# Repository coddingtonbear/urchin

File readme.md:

# Urchin: Atmel Programmer with onboard 8-pin ATTiny pad

Everybody makes their own programmer someday.  What this does in addition
to all of the normal things you'd expect a programmer to do is include
an 8-pin ATTiny pad allowing you to program an ATTiny on-the-fly by
pressing it onto the unpopulated pad during programming.

## Schematic

## Fuse Settings

We need slightly-nonstandard fuse settings so we can run both the microcontroller
and the CH340 UART to USB adapter using the same 12MHz clock; these will differ
from the default 12MHz settings in only the Low bit having CKOUT enabled.

* Low: 0xbf
* High: 0xde
* Extended: 0xfd

## Enclosure

You can also find a 3d-printable enclosure in the 'enclosure' folder.

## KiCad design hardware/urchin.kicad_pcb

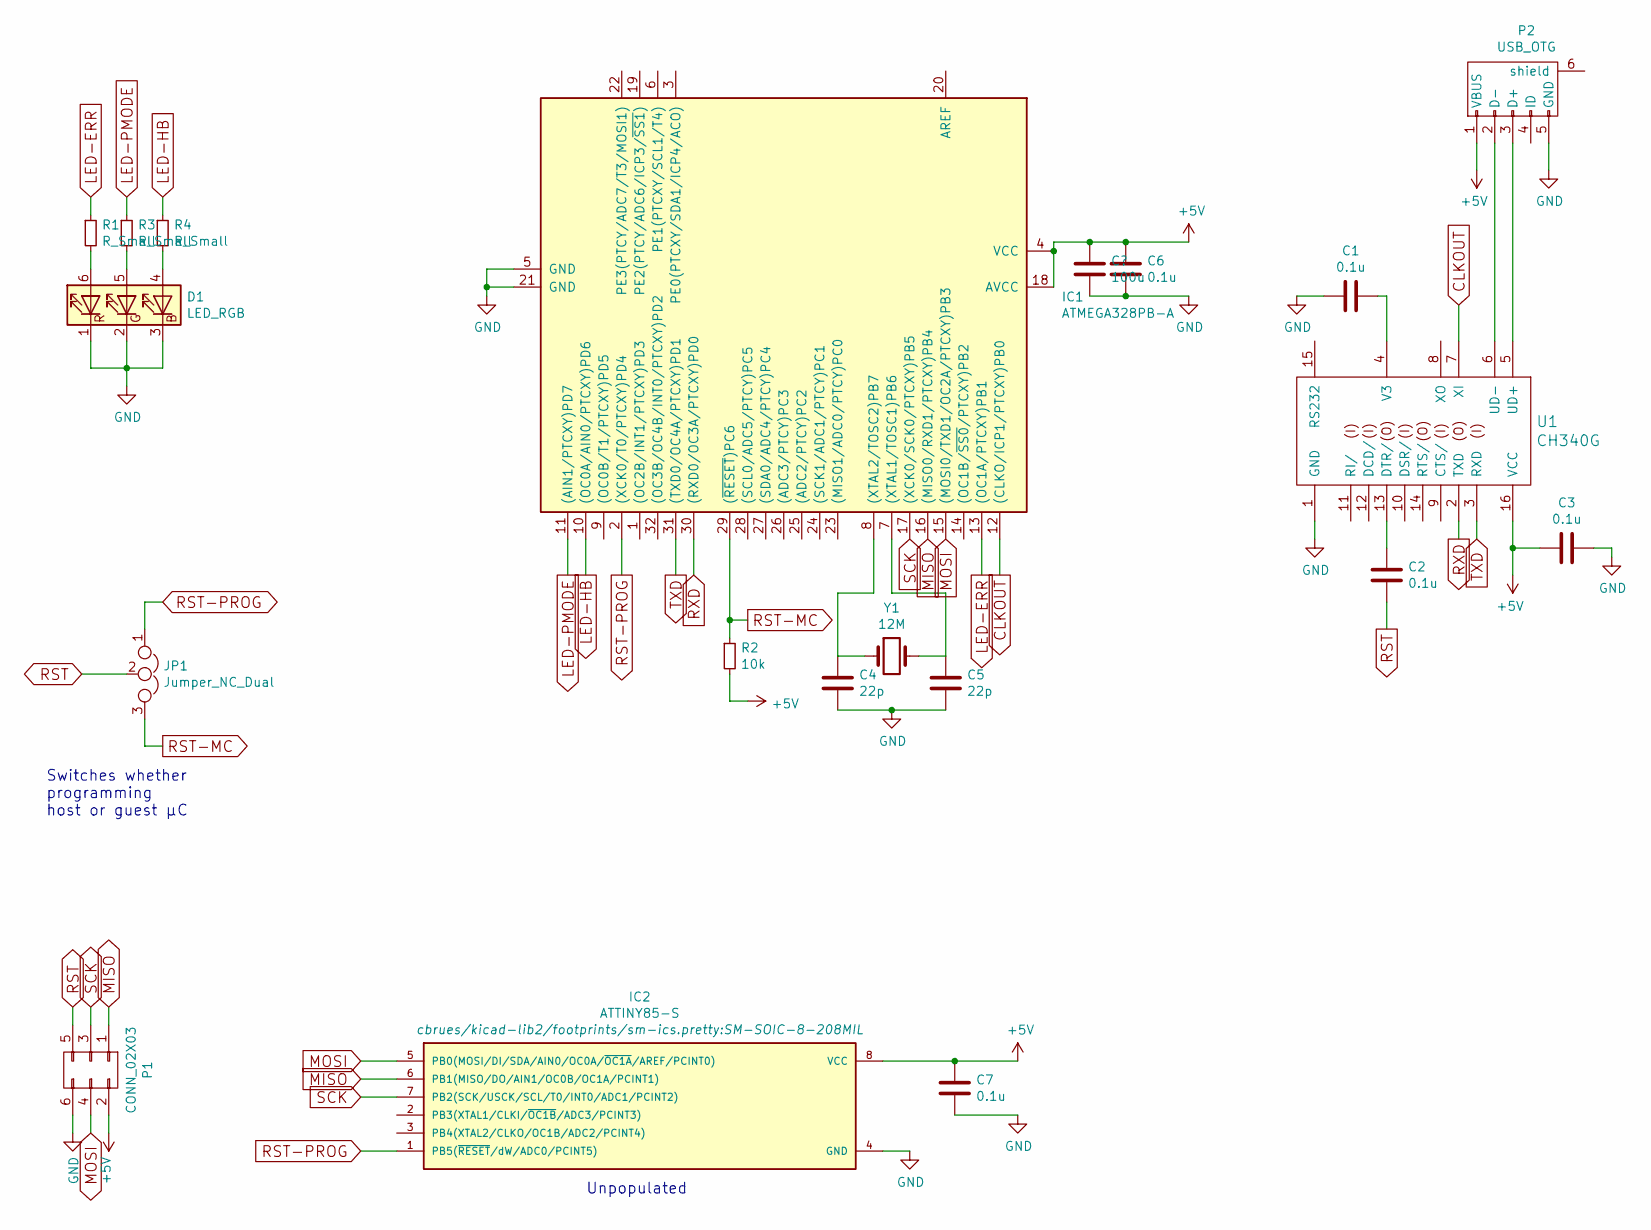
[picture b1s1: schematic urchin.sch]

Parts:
C1, C2, C3, C6, C7: 0.1u; C_0805_HandSoldering
C4, C5: 22p; C_0805_HandSoldering
D1: LED_RGB; SLV6A-FKB
IC1: ATMEGA328PB-A; TQFP32_ATMEGA328P
IC2: ATTINY85-S; SM-SOIC-8-208MIL
JP1: Jumper_NC_Dual; Pin_Header_Straight_1x03_Pitch2.54mm_SMD_Pin1Left
P1: CONN_02X03; SMD_PIN_HEADER_02x03
P2: USB_OTG; MICRO-B_USB-INVERTED
R1, R3, R4: R_Small; R_0805_HandSoldering
R2: 10k; R_0805_HandSoldering
U1: CH340G; SOIC-16_3.9x9.9mm_Pitch1.27mm
Y1: 12M; Crystal_SMD_HC49-SD

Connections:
+5V: C3.1, C6.1, C7.1, IC1.4 (VCC), IC1.18 (AVCC), IC2.8 (VCC), P1.2, P2.1 (VBUS), R2.2, U1.16 (VCC); also elsewhere on the board
CLKOUT: IC1.12 ((CLKO/ICP1/PTCXY)PB0), U1.7 (XI)
GND: C1.1, C3.2, C4.2, C5.2, C6.2, C7.2, D1.1 (RK), D1.2 (GK), D1.3 (BK), IC1.5 (GND), IC1.21 (GND), IC2.4 (GND), P1.6, P2.5 (GND), U1.1 (GND); also elsewhere on the board
LED-ERR: IC1.13 ((OC1A/PTCXY)PB1), R1.1
LED-HB: IC1.10 ((OC0A/AIN0/PTCXY)PD6), R4.1
LED-PMODE: IC1.11 ((AIN1/PTCXY)PD7), R3.1
MISO: IC1.16 ((MISO0/RXD1/PTCXY)PB4), IC2.6 (PB1(MISO/DO/AIN1/OC0B/OC1A/PCINT1)), P1.1
MOSI: IC1.15 ((MOSI0/TXD1/OC2A/PTCXY)PB3), IC2.5 (PB0(MOSI/DI/SDA/AIN0/OC0A/~OC1A~/AREF/P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), P1.4
unnamed: C1.2, U1.4 (V3)
unnamed: C2.1, U1.13 (DTR/)
unnamed: C4.1, IC1.8 ((XTAL2/TOSC2)PB7), Y1.1
unnamed: C5.1, IC1.7 ((XTAL1/TOSC1)PB6), Y1.2
unnamed: D1.4 (BA), R4.2
unnamed: D1.5 (GA), R3.2
unnamed: D1.6 (RA), R1.2
unnamed: P2.2 (D-), U1.6 (UD-)
unnamed: P2.3 (D+), U1.5 (UD+)
RST: C2.2, JP1.2, P1.5
RST-MC: IC1.29 ((~RESET~)PC6), JP1.3, R2.1
RST-PROG: IC1.2 ((XCK0/T0/PTCXY)PD4), IC2.1 (PB5(~RESET~/dW/ADC0/PCINT5)), JP1.1
RXD: IC1.30 ((RXD0/OC3A/PTCXY)PD0), U1.2 (TXD)
SCK: IC1.17 ((XCK0/SCK0/PTCXY)PB5), IC2.7 (PB2(SCK/USCK/SCL/T0/INT0/ADC1/PCINT2)), P1.3
TXD: IC1.31 ((TXD0/OC4A/PTCXY)PD1), U1.3 (RXD)

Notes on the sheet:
Switches whether programming host or guest µC
Unpopulated

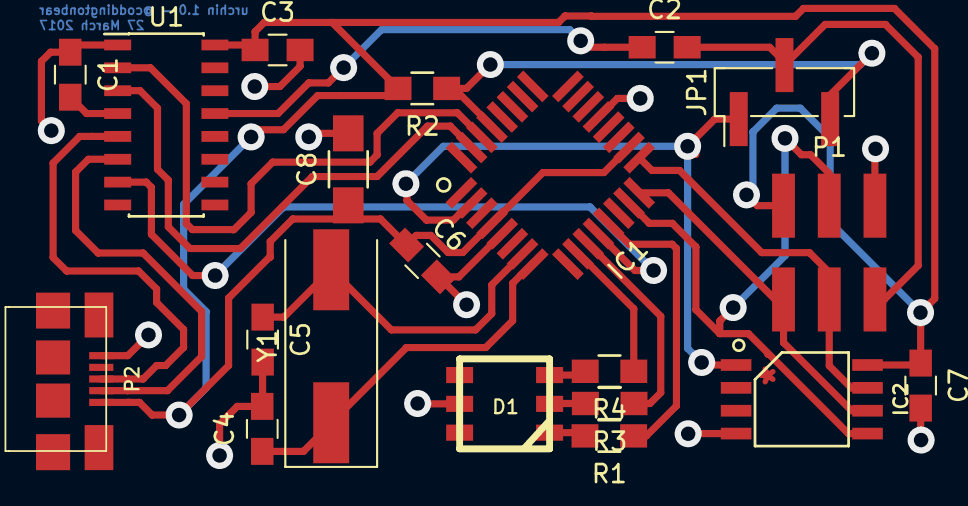
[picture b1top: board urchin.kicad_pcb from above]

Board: 2 copper layers, 20 parts (0 on the bottom side), 23 nets.

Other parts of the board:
C8: 100u; R_1206_HandSoldering

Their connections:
+5V: C8.1; also elsewhere on the board
GND: C8.2; also elsewhere on the board

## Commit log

2017-02-20 Updating hardware to latest revision.
2017-02-20 Adding keepout area below crystal.
2017-02-20 Adding alignment markers; plots.
2017-02-20 Centering
2017-02-20 Adding new 100uF reservoir capacitor.
2017-02-20 Removing some files that should've always been hidden.
2017-02-20 Removing generated plots.
2017-02-20 Saving unknown changes...
2017-02-20 Adding new schematic to readme.
2017-03-27 Updating schematic to include name/date; minor changes.
2017-04-03 Updating to latest hardware file.
2017-04-04 Adding enclosure STLs; updating readme slightly, etc.
2017-04-04 Recommending T-Glase for filament.
